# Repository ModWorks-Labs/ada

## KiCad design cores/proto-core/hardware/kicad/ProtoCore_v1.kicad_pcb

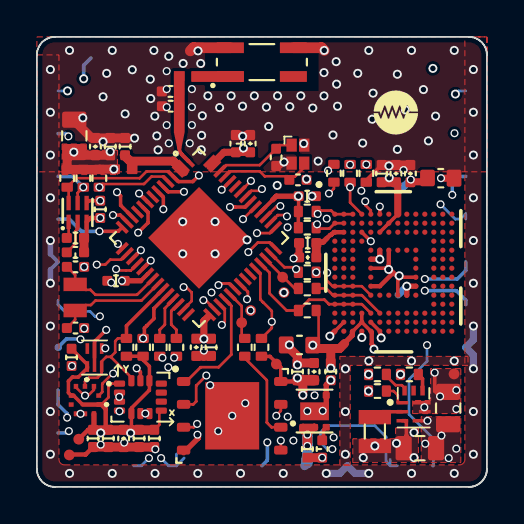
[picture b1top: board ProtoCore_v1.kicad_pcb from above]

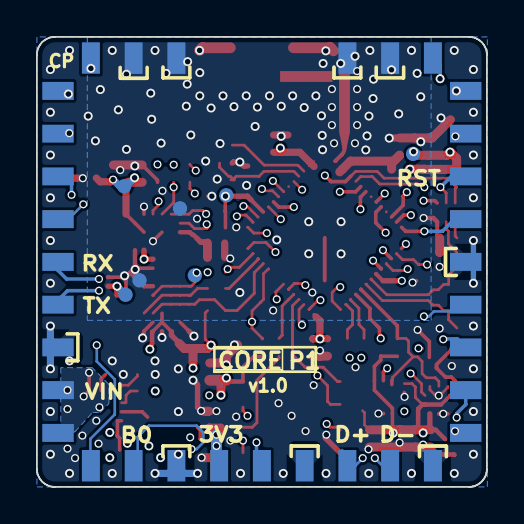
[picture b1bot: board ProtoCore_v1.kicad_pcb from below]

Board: 6 copper layers, 25.0 x 25.0 mm, 90 parts (7 on the bottom side), 63 nets.

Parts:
ANT1: XDCR_2450AT42E010B001E; 2450AT42E010B001E
C1, C17: 10u; C_0805_2012Metric_MW
C2, C13: 10p; C_0402_1005Metric_MW
C3, C14: 12p; C_0402_1005Metric_MW
C4, C6, C7, C18, C28, C32, C33, C38: 1u; C_0402_1u_MW
C5, C8, C9, C10, C11, C21, C22, C24, C25, C26, C29, C30, C31, C35, C37, C39, C40: 100n; C_0402_100n_MW
C12, C19, C23: 10n; C_0402_10n_MW
C15, C16: DNP; C_0402_1005Metric_MW
C20: 22u; C_0805_2012Metric_MW
C27, C34: 4u7; C_0603_1608Metric_MW
L1: 2n; L_0402_1005Metric_MW
L2: 1u5; L_0402_1005Metric_MW
L3: 1u; 74479276210C
MOD1: ADA_Core_Underside_Pads
R1, R2, R14, R15: 10k; R_0402_1005Metric_MW
R3, R4: 4k7; R_0402_1005Metric_MW
R5, R6, R8: 22R; R_0402_1005Metric_MW
R7: 499R; R_0402_1005Metric_MW
R9: 0R; R_0402_1005Metric_MW
R10: 40k2; R_0402_1005Metric_MW
R11, R13: 100k; R_0402_1005Metric_MW
R12: 249k; R_0402_1005Metric_MW
R17, R19, R20, R21, R22: 47k; R_0402_1005Metric_MW
TP2, TP3, TP7, TP12, TP13, TP21, TP22: TestPointPad; TestPoint_Pad_D0.8mm_MW
TP8, TP9, TP11, TP14, TP15, TP18, TP19, TP20: TestPointPad; TestPoint_Pad_D0.6mm_MW
U1: ESP32-S3R8; ESP32-S3_Small-EP
U2: TPS62902RPJR
U3: TPS22810DRV; WSON-6-1EP_2x2mm_P0.65mm_EP1x1.6mm_MW
U4: TPS3899DL30DSER
U5: M24C02-FMH6TG; M24C32FMH6TG
U6: W25Q128JVP; W25Q-WSON-8
U7: EMMC04G-CT32_4-Line
U8: LSM6DSO32TR; LGA-14_3x2.5mm_P0.5mm_MW
U10: BMP390
Y1: CM8V-T1A-32.768KHZ-7PF-20PPM-TA-QC; CM8V-T1A-32.768KHZ-7PF-20PPM-TA-QC_XTAL_CM8V-T1A-32.768KHZ-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
Y2: ABM12W-40MHZ-8-B1U-T3; XTAL_ABM12W-40.0000MHZ-8-B1U-T3

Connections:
3V3_AUX_EN: R11.2, U1.38 (GPIO33), U3.5 (EN)
+3V3: C1.1, C4.1, C5.1, C6.1, C7.1, C9.1, C10.1, C11.1, C12.1, C18.1, C20.1, C22.1, C25.1, C26.1, C27.1, C28.1, C29.1, C30.1, C32.1, C34.1, C35.1, C37.1, C38.1, C39.1, C40.1, L1.1, L3.2, R1.1, R3.1, R4.1, R11.1, R13.2, R14.1, R15.1, R17.2, R19.2, R20.2, R21.2, R22.2, TP2.1, TP13.1, TP18.1, TP19.1, TP21.1, TP22.1, U1.20 (VDD3P3_RTC), U1.29 (VDD_SPI), U1.46 (VDD3P3_CPU), U1.55 (VDDA), U1.56 (VDDA), U2.3 (VOS), U3.6 (VIN), U4.4 (VDD), U5.1 (VCC), U6.8 (VDD), U7.C6 (VCCQ), U7.E6 (VCC), U7.F5 (VCC), U7.J10 (VCC), U7.K9 (VCC), U7.M4 (VCCQ), U7.N4 (VCCQ), U7.P3 (VCCQ), U7.P5 (VCCQ), U8.1 (SDO), U8.5 (VDDIO), U8.8 (VDD), U8.12 (CS), U10.1 (VDDIO), U10.6 (CSB), U10.10 (VDD)
+3V3_AUX: C21.1, MOD1.31, U3.1 (VOUT), U3.2 (QOD)
/External Interface/RF_FEED_ANT: ANT1.1, L2.2
/Microcontroller/BOOT1: R2.1, U1.52 (BOOT1/GPIO46)
/Microcontroller/CLK_MAIN_IN: C3.1, U1.54 (XTAL_40M_P), Y2.1
/Microcontroller/CLK_MAIN_OUT: C14.1, U1.53 (XTAL_40M_N), Y2.3
/Microcontroller/CLK_RTC_IN: C2.1, U1.21 (XTAL_32K_P), Y1.1
/Microcontroller/CLK_RTC_OUT: C13.1, U1.22 (XTAL_32K_N), Y1.2
/Microcontroller/EMMC_CLK_MCU: R8.1, TP14.1, U1.40 (GPIO35)
/Microcontroller/QSPI_CLK_MCU: R9.1, TP8.1, U1.33 (GPIO30/SPICLK)
/Microcontroller/UART0_RX_MCU: R7.1, U1.50 (GPIO44/U0RXD)
/Microcontroller/USB_MCU_D+: R6.1, U1.26 (GPIO20/USB_D+)
/Microcontroller/USB_MCU_D-: R5.1, U1.25 (GPIO19/USB_D-)
/Microcontroller/VDD_PI_OUT: C8.1, L1.2, U1.2 (VDD3P3), U1.3 (VDD3P3)
/Power Management/3V3_AUX_CT: C19.1, U3.3 (CT)
/Power Management/REG_CFG: R10.1, U2.7 (SCONF)
/Power Management/REG_FB: R12.1, U2.9 (FB)
/Power Management/REG_PG: R13.1, U2.1 (PG)
/Power Management/REG_SW: L3.1, U2.2 (SW)
/Power Management/SUP_CTR: C24.1, U4.1 (CTR)
/Power Management/SUP_CTS: C23.1, U4.2 (CTS)
CORE_BOOT_SEL: MOD1.29, R1.2, U1.5 (BOOT0/GPIO0)
CORE_RESET_N: MOD1.7, R14.2, U4.5 (SNS)
CORE_RST_REQ_N: R15.2, TP3.1, U1.4 (CHIP_PU), U4.6 (RST_N), U7.K5 (RST_N)
EMMC_CLK: R8.2, U7.M6 (CLK)
EMMC_CMD: R17.1, U1.39 (GPIO34), U7.M5 (CMD)
EMMC_DAT0: R21.1, U1.43 (GPIO38), U7.A3 (DAT0)
EMMC_DAT1: R20.1, U1.44 (GPIO39/MTCK), U7.A4 (DAT1)
EMMC_DAT2: R19.1, U1.41 (GPIO36), U7.A5 (DAT2)
EMMC_DAT3: R22.1, U1.42 (GPIO37), U7.B2 (DAT3)
GND: ANT1.3, ANT1.4, C1.2, C2.2, C3.2, C4.2, C5.2, C6.2, C7.2, C8.2, C9.2, C10.2, C11.2, C12.2, C13.2, C14.2, C15.2, C16.2, C17.2, C18.2, C19.2, C20.2, C21.2, C22.2, C23.2, C24.2, C25.2, C26.2, C27.2, C28.2, C29.2, C30.2, C31.2, C32.2, C33.2, C34.2, C35.2, C37.2, C38.2, C39.2, C40.2, MOD1.5, MOD1.11, MOD1.12, MOD1.16, MOD1.17, MOD1.25, MOD1.30, MOD1.33, MOD1.36, R2.2, R10.2, R12.2, TP7.1, TP9.1, TP12.1, TP15.1, TP20.1, U1.57 (GND), U2.4 (GND), U3.4 (GND), U3.7 (GND), U4.3 (GND), U5.2 (GND), U6.4 (GND), U6.9 (EP), U7.A6 (VSS), U7.C4 (VSSQ), U7.E7 (VSS), U7.G5 (VSS), U7.H10 (VSS), U7.J5 (VSS), U7.K8 (VSS), U7.N2 (VSSQ), U7.N5 (VSSQ), U7.P4 (VSSQ), U7.P6 (VSSQ), U8.2 (SDX), U8.3 (SCX), U8.6 (GND), U8.7 (GND__1), U10.3 (GND), U10.5 (SDO), U10.8 (VSS_2), U10.9 (VSS_3), Y2.2 (GND), Y2.4 (GND__1)
I2C0_SCL: R4.2, U1.24 (GPIO18), U5.4 (SCL), U8.13 (SCL), U10.2 (SCL)
I2C0_SDA: R3.2, U1.23 (GPIO17), U5.3 (SDA), U8.14 (SDA), U10.4 (SDA)
INT_IMU: U1.27 (GPIO21), U8.4 (INT1)
IO0: MOD1.22, U1.6 (GPIO1)
IO1: MOD1.21, U1.7 (GPIO2)
IO2: MOD1.10, U1.9 (GPIO4)
IO3: MOD1.32, U1.10 (GPIO5)
IO4: MOD1.9, U1.12 (GPIO7)
IO5: MOD1.8, U1.13 (GPIO8)
IO6: MOD1.6, U1.14 (GPIO9)
IO7: MOD1.2, U1.15 (GPIO10)
IO8: MOD1.3, U1.16 (GPIO11)
IO9: MOD1.28, U1.17 (GPIO12)
IO10: MOD1.1, U1.18 (GPIO13)
IO11: MOD1.4, U1.19 (GPIO14)
IO14: MOD1.20, U1.45 (GPIO40/MTDO)
IO15: MOD1.19, U1.47 (GPIO41/MTDI)
IO16: MOD1.18, U1.48 (GPIO42/MTMS)
unnamed: C31.1, C33.1, U7.C2 (VDDI)
QSPI_CLK: R9.2, U6.6 (CLK)
QSPI_CS: U1.32 (GPIO29/SPICS0), U6.1 (CS)
QSPI_IO0: U1.35 (GPIO32/SPID), U6.5 (IO0)
QSPI_IO1: U1.34 (GPIO31/SPIQ), U6.2 (IO1)
QSPI_IO2: U1.31 (GPIO28/SPIWP), U6.3 (IO2/WP)
QSPI_IO3: U1.30 (GPIO27/SPIHD), U6.7 (IO3/HD)
RF_FEED: C15.1, C16.1, L2.1, U1.1 (LNA_IN)
UART0_RX: MOD1.23, R7.2
UART0_TX: MOD1.24, U1.49 (GPIO43/U0TXD)
USB_D+: MOD1.34, R6.2
USB_D-: MOD1.35, R5.2
VIN: C17.1, MOD1.26, MOD1.27, TP11.1, U2.5 (EN), U2.6 (VIN)

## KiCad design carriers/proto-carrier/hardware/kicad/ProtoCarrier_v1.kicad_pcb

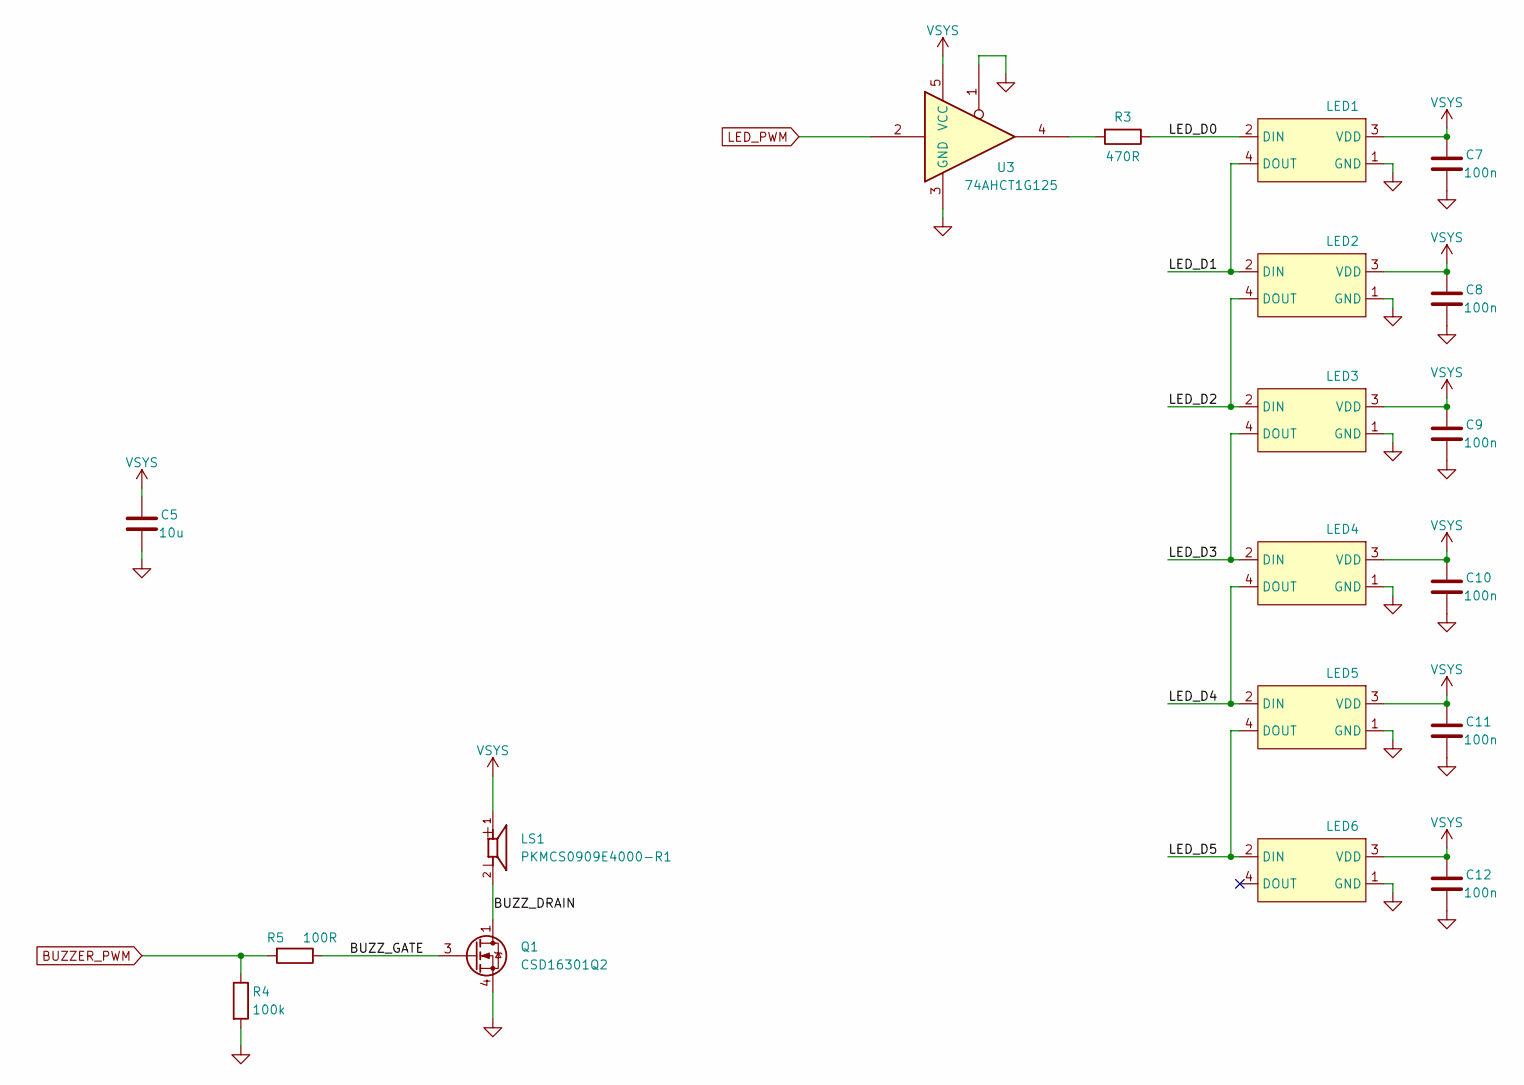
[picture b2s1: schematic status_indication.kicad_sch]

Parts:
C5: 10u; C_0805_2012Metric_MW
C7, C8, C9, C10, C11, C12: 100n; C_0402_100n_MW
LED1, LED2, LED3, LED4, LED5, LED6: XL-1615RGBC-2812B
LS1: PKMCS0909E4000-R1; PKMCS0909E4000-R1_SPKR_PKMCS0909E4000-R1; PARTREV May 22, 2020
Q1: CSD16301Q2; Texas_DQK
R3: 470R; R_0402_1005Metric
R4: 100k; R_0402_1005Metric
R5: 100R; R_0402_1005Metric
U3: 74AHCT1G125; SOT-23-5

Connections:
/Status Indication/BUZZ_DRAIN: LS1.2, Q1.1 (D), Q1.2 (D), Q1.5 (D), Q1.6 (D), Q1.8 (D)
/Status Indication/BUZZ_GATE: Q1.3 (G), R5.1
/Status Indication/LED_D0: LED1.2 (DIN), R3.1
/Status Indication/LED_D1: LED1.4 (DOUT), LED2.2 (DIN)
/Status Indication/LED_D2: LED2.4 (DOUT), LED3.2 (DIN)
/Status Indication/LED_D3: LED3.4 (DOUT), LED4.2 (DIN)
/Status Indication/LED_D4: LED4.4 (DOUT), LED5.2 (DIN)
/Status Indication/LED_D5: LED5.4 (DOUT), LED6.2 (DIN)
BUZZER_PWM: R4.1, R5.2; also elsewhere on the board
GND: C5.2, C7.2, C8.2, C9.2, C10.2, C11.2, C12.2, LED1.1 (GND), LED2.1 (GND), LED3.1 (GND), LED4.1 (GND), LED5.1 (GND), LED6.1 (GND), Q1.4 (S), Q1.7 (S), R4.2, U3.1, U3.3 (GND); also elsewhere on the board
LED_PWM: U3.2; also elsewhere on the board
unnamed: R3.2, U3.4
VSYS: C5.1, C7.1, C8.1, C9.1, C10.1, C11.1, C12.1, LED1.3 (VDD), LED2.3 (VDD), LED3.3 (VDD), LED4.3 (VDD), LED5.3 (VDD), LED6.3 (VDD), LS1.1, U3.5 (VCC); also elsewhere on the board

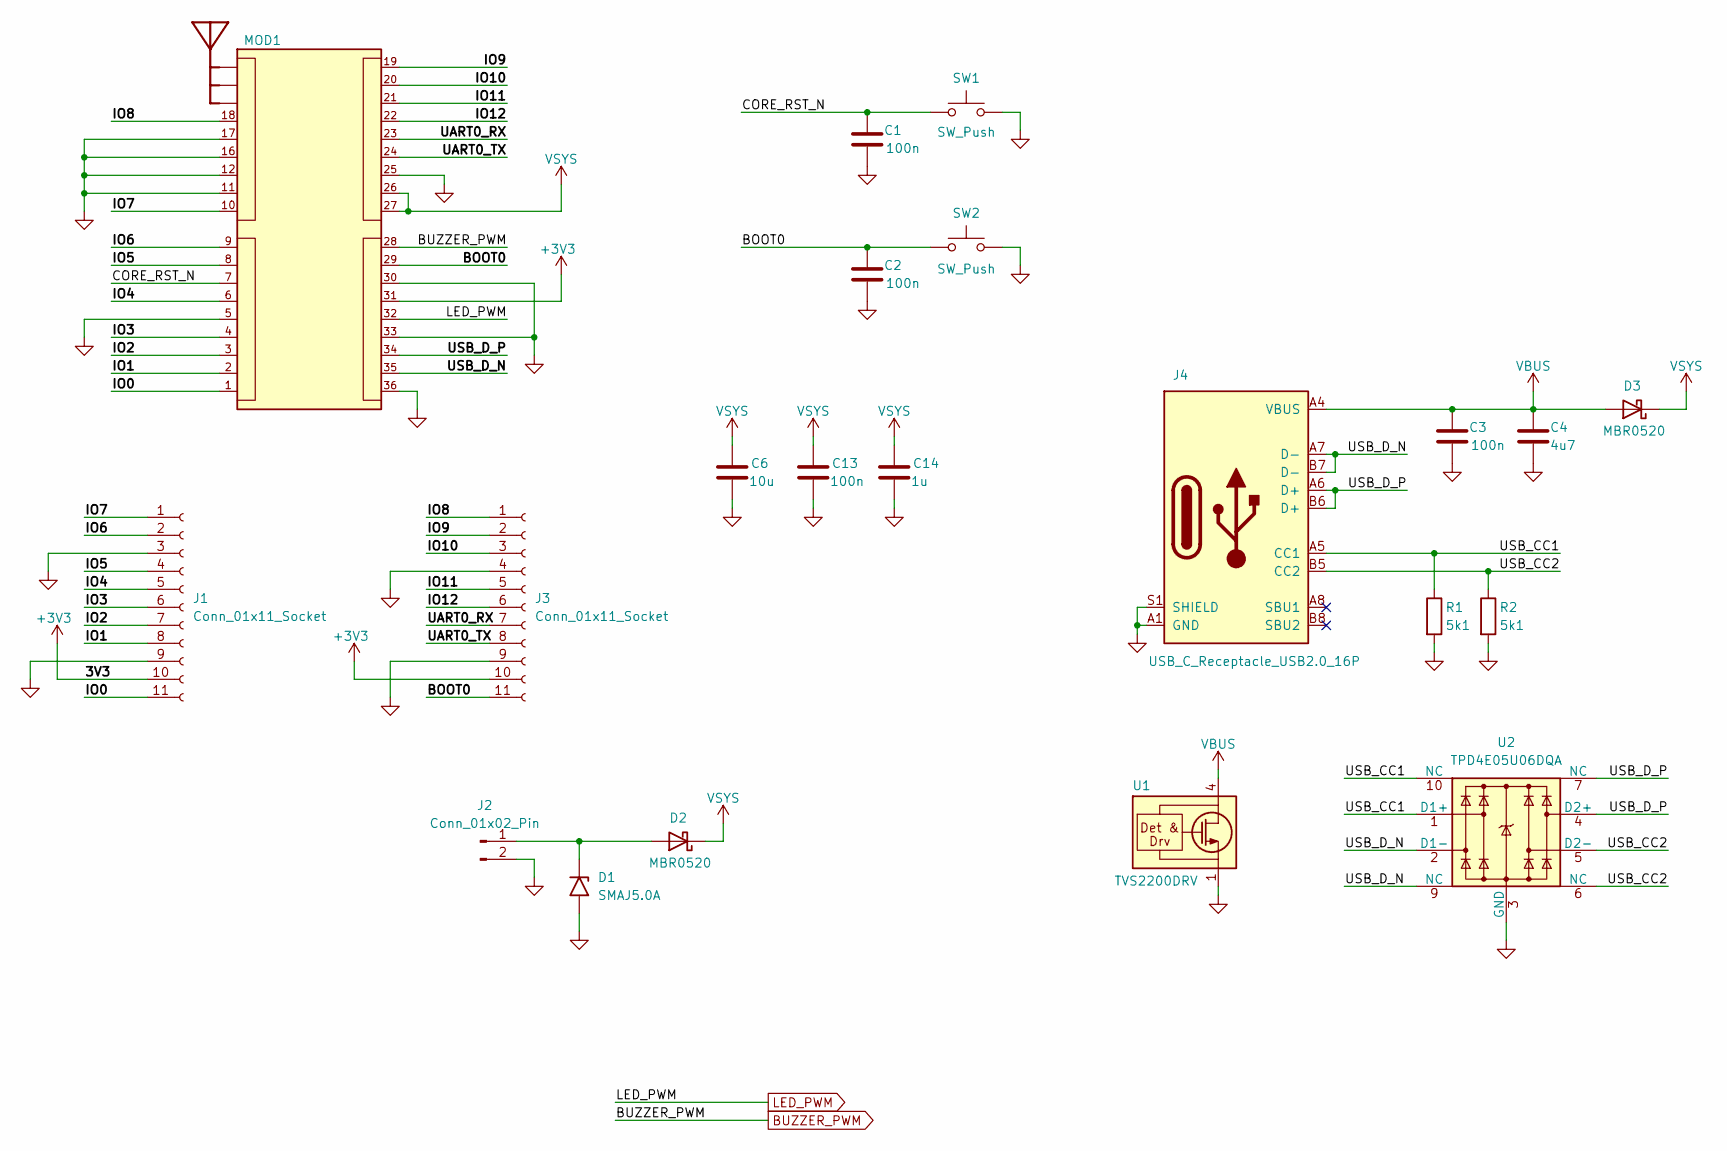
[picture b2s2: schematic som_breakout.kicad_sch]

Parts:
C1, C2, C3: 100n; C_0402_100n_MW
C4: 4u7; C_0603_1608Metric_MW
C6: 10u; C_0805_2012Metric_MW
C13: 100n; C_0402_1005Metric_MW
C14: 1u; C_0603_1608Metric_MW
D1: SMAJ5.0A; D_SMA
D2, D3: MBR0520; D_SOD-123
J1, J3: Conn_01x11_Socket; PinSocket_1x11_P2.54mm_Vertical
J2: Conn_01x02_Pin; PinHeader_1x02_P2.54mm_Vertical
J4: USB_C_Receptacle_USB2.0_16P; USB_C_Receptacle_GCT_USB4105-xx-A_16P_TopMnt_Horizontal
MOD1: Proto_Core_Carrier_Pads
R1, R2: 5k1; R_0402_1005Metric
SW1, SW2: SW_Push; SKRPABE010_SW_SKRPABE010
U1: TVS2200DRV; WSON-6-1EP_2x2mm_P0.65mm_EP1x1.6mm
U2: TPD4E05U06DQA; USON-10_2.5x1.0mm_P0.5mm

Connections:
+3V3: J1.10, J3.10, MOD1.31
/SoM Breakout/BOOT0: C2.1, J3.11, MOD1.29, SW2.1, SW2.2
/SoM Breakout/CORE_RST_N: C1.1, MOD1.7, SW1.1, SW1.2
/SoM Breakout/IO0: J1.11, MOD1.1
/SoM Breakout/IO1: J1.8, MOD1.2
/SoM Breakout/IO2: J1.7, MOD1.3
/SoM Breakout/IO3: J1.6, MOD1.4
/SoM Breakout/IO4: J1.5, MOD1.6
/SoM Breakout/IO5: J1.4, MOD1.8
/SoM Breakout/IO6: J1.2, MOD1.9
/SoM Breakout/IO7: J1.1, MOD1.10
/SoM Breakout/IO8: J3.1, MOD1.18
/SoM Breakout/IO9: J3.2, MOD1.19
/SoM Breakout/IO10: J3.3, MOD1.20
/SoM Breakout/IO11: J3.5, MOD1.21
/SoM Breakout/IO12: J3.6, MOD1.22
/SoM Breakout/UART0_RX: J3.7, MOD1.23
/SoM Breakout/UART0_TX: J3.8, MOD1.24
/SoM Breakout/USB_CC1: J4.A5 (CC1), R1.1, U2.1 (D1+), U2.10 (NC)
/SoM Breakout/USB_CC2: J4.B5 (CC2), R2.1, U2.5 (D2-), U2.6 (NC)
/SoM Breakout/USB_D_N: J4.A7 (D-), J4.B7 (D-), MOD1.35, U2.2 (D1-), U2.9 (NC)
/SoM Breakout/USB_D_P: J4.A6 (D+), J4.B6 (D+), MOD1.34, U2.4 (D2+), U2.7 (NC)
BUZZER_PWM: MOD1.28; also elsewhere on the board
GND: C1.2, C2.2, C3.2, C4.2, C6.2, C13.2, C14.2, D1.2 (A2), J1.3, J1.9, J2.2, J3.4, J3.9, J4.A1 (GND), J4.A12 (GND), J4.B1 (GND), J4.B12 (GND), J4.S1 (SHIELD), MOD1.5, MOD1.11, MOD1.12, MOD1.16, MOD1.17, MOD1.25, MOD1.30, MOD1.33, MOD1.36, R1.2, R2.2, SW1.3, SW1.4, SW2.3, SW2.4, U1.1 (GND), U1.2 (GND), U1.3 (GND), U1.7 (GND), U2.3 (GND), U2.8 (GND); also elsewhere on the board
LED_PWM: MOD1.32; also elsewhere on the board
unnamed: D1.1 (A1), D2.2 (A), J2.1
VBUS: C3.1, C4.1, D3.2 (A), J4.A4 (VBUS), J4.A9 (VBUS), J4.B4 (VBUS), J4.B9 (VBUS), U1.4 (IN), U1.5 (IN), U1.6 (IN)
VSYS: C6.1, C13.1, C14.1, D2.1 (K), D3.1 (K), MOD1.26, MOD1.27; also elsewhere on the board

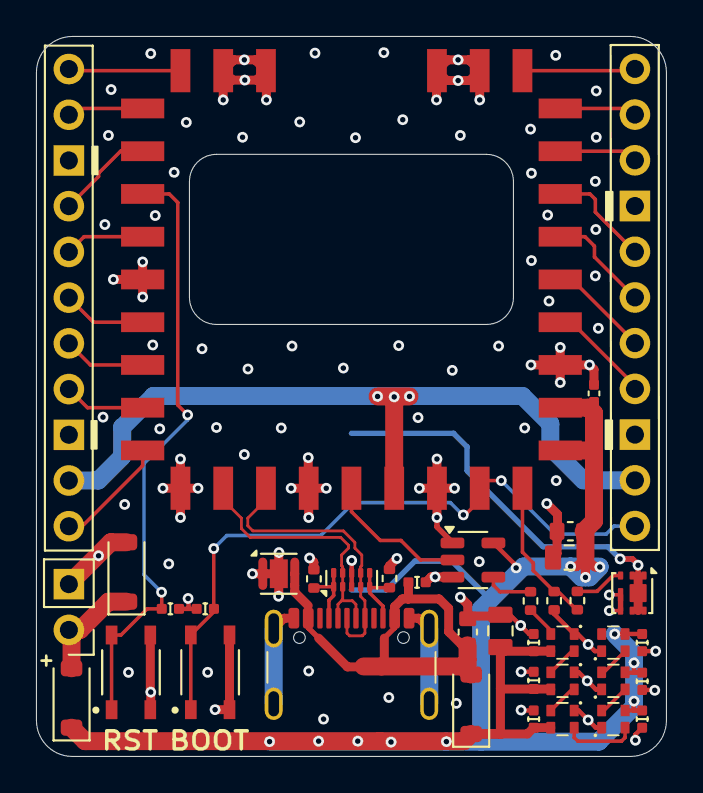
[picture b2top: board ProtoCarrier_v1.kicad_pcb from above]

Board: 4 copper layers, 35.0 x 40.0 mm, 40 parts (1 on the bottom side), 37 nets.

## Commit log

2025-12-23 initial repo scaffold
2025-12-23 update gitignore
2025-12-23 added kicad files, fab files and diagrams
2025-12-23 updated .gitignore
2025-12-23 Stop tracking .vscode
2025-12-29 initial pre-assembly file dump
2025-12-30 minor updates
2025-12-30 Added tuned hotplate reflow procedure and assembly checklist
2026-01-01 Initial firmware
